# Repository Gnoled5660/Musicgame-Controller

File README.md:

# Musicgame-Controller

# Description
This is an arcade like controller, designed for the Musicgame by bakedcloudz (GitHub Repo: https://github.com/wuelaineyuan-bit/MUSICGAME). It has four interactive buttons and one joystick. Next to these features, it also has a speaker on the side and a tft display. While the controller is inactive or is not being used, it will play a retro arcade like music in the background. All this is powered by a Raspberry Pi Pico 2.

# Motivation
The reason we designed this was because bakedcloudz project lacked of an interactive controller for her arcade game. Therefore, we wanted to design another controller for that project. This project is a sub project of the main project MUSICGAME (GitHub Repo: https://github.com/wuelaineyuan-bit/MUSICGAME). 

# PCB and Schematic
The PCB and schematic was made with KiCAD. Schematic is rather simple: Connect the pins to the buttons and joysticks. As almost every Pico 2 pin is a GPIO pin, almost every pin could be used to connect to the amplifier and tft module. 

This PCB is a rather simple PCB, where the premade modules are soldered on top of it. There are no components that need to be preassembled. All the components are big enough to be soldered by hand. 

This PCB is a two layer PCB, where the red tracks function as signal tracks and the blue tracks as power supply tracks.

# Firmware
The firmware was written in micropython. Most of libraries are standard libraries provided by micropico. However, we had to download an external library for the tft display. The program begins with playing a retro music until one button is clicked. Then, it stops playing the music in a loop and starts listening to the actions that the user might take. Once a button or the joystick is pressed, it sends a message to the computer with the print() function. The other projects code has to read the lines with serial.readline() to decide which actions to make next.

# Assembling
There are a few components that need to be screwed on to the board. These components include the PCB, the joystick and the display. Because of that, we designed some holes, where heat threaded inserts can be placed. All components use M3 screws besides the joystick. The joystick requires M5 screws. The buttons can be simply pressed into the holes, which means it doesnt require any screws. 

Many components need to be soldered on to the PCB too. It is recommended to use header pins between the Pico 2 board and the PCB. After everything is soldered, you need the connection cables to connect the PCB with the buttons and joysticks. Another cable is used to connect the amplifier with the speaker.

Depending on whether you want to color the music notes, there two versions of this controller. As a usual 3D printer cannot print two colors at the same time, the music notes have to be painted later by hand, if they should be colored black.

# Zine

# BOM
|Name                   |Description                  |Links                                                                                                                                                                                                                                                                                                                                                                                                                            |Quantity|Cost |
|-----------------------|-----------------------------|---------------------------------------------------------------------------------------------------------------------------------------------------------------------------------------------------------------------------------------------------------------------------------------------------------------------------------------------------------------------------------------------------------------------------------|--------|-----|
|PCB                    |Printed Circuit Board        |https://jlcpcb.com                                                                                                                                                                                                                                                                                                                                                                                                               |1       |6    |
|Speaker                |8Ohm 1W Speaker              |https://botland.de/analoge-lautsprecher/19458-lautsprecher-1w-8ohm-30x20x5mm-adafruit-4227-5904422354848.html?gad_source=1&gad_campaignid=23574294202&gbraid=0AAAAApBhtfdmZRY2FJGh-xArvpZV2eCLa&gclid=CjwKCAjw9NjRBhATEiwA_p2J8S86mPfKDnuq3Meckbowv6KXXqRWsGLSo_4u3SZHp3daIj2UEHCkihoC-4IQAvD_BwE                                                                                                                                |1       |3.20 |
|MAX98357A              |Amplifier                    |https://www.amazon.de/Verstärker-Verstärkerplatine-Elektronische-Enthusiasten-Ingenieure/dp/B0F1TRSD2N/ref=asc_df_B0F1TRSD2N?mcid=b3cc78920c783042ac17388eb574bcae&th=1&psc=1&tag=googshopde-21&linkCode=df0&hvadid=751200241164&hvpos=&hvnetw=g&hvrand=557849342057074083&hvpone=&hvptwo=&hvqmt=&hvdev=c&hvdvcmdl=&hvlocint=&hvlocphy=9192175&hvtargid=pla-2419607785174&psc=1&hvocijid=557849342057074083-B0F1TRSD2N-&hvexpln=0|1       |8    |
|Pico 2                 |Microcontroller              |https://www.reichelt.de/de/de/shop/produkt/raspberry_pi_pico_2_rp235x_cortex-m33_microusb-383358?PROVID=2788&gad_source=1&gad_campaignid=18342381572&gbraid=0AAAAADwnxtZySp6snfqlNQh9cQN6eEoma&gclid=CjwKCAjw9NjRBhATEiwA_p2J8Z5EgQVT_I2qJDtdCrQ07205wtKj9qcaRFiQCRmb6aA3hme78elB0xoCkwoQAvD_BwE                                                                                                                                 |1       |5.14 |
|Arcade Button          |Button                       |https://www.berrybase.de/mini-arcade-button-24mm/farbe-rot?gad_source=1&gad_campaignid=22735754544&gbraid=0AAAAADSQJK6oAGUJjXrYG5gYnJHQ5Jjam&gclid=CjwKCAjw9NjRBhATEiwA_p2J8TrWjbhcsVNdGDTCZIJtp7aCs2650nWhUSuZ5SYqhxaVa3eP51LD4BoCi0oQAvD_BwE                                                                                                                                                                                   |4       |4.13 |
|Joystick               |Joystick to control direction|https://de.aliexpress.com/item/1005006881757851.html?spm=a2g0o.tesla.0.0.5f0cIGAYIGAYAg&pdp_npi=6%40dis%21EUR%2110%2C38€%214%2C69€%21%21%21%21%21%40211b6c1717819569630011453e4670%2112000038607187018%21btfpre%21%21%21%211%210%21&pvid=210f2bc9-ea8b-413f-9403-466b57ef5987&afTraceInfo=1005006881757851__pc__c_ppc_item_bridge_pc_same_wf__r6YWpYS__1781956963362&gatewayAdapt=glo2deu                                        |1       |12.61|
|5 Pin JST-XH           |Receptacle for Joystick      |https://www.reichelt.de/de/de/shop/produkt/jst_-_stiftleiste_gerade_1x5-polig_-_xh-185076?PROVID=2788&gad_source=1&gad_campaignid=21154722893&gbraid=0AAAAADwnxtbPyJx8nCOWbAD8uZL35tp4z&gclid=CjwKCAjw9NjRBhATEiwA_p2J8V1nQh1DAOTZbzkY9tsnYV5dJ24D084mqzUnY8sjf2c5BYI_QxigaBoCw18QAvD_BwE                                                                                                                                        |1       |0.34 |
|2 Pin JST-XH           |Receptacle for Buttoms       |https://www.berrybase.de/ph2.0-buchse-printmontage-gerade-2-pin?gad_source=1&gad_campaignid=22735754544&gbraid=0AAAAADSQJK6oAGUJjXrYG5gYnJHQ5Jjam&gclid=CjwKCAjw9NjRBhATEiwA_p2J8Urol7tXOTt939yNAB6z-nwgtlo3U0Lzd1b4rYRmLl3-F9V2eJTBkRoC8gwQAvD_BwE                                                                                                                                                                              |4       |0.46 |
|2 Pin JST-XH cable     |Cable                        |https://www.berrybase.de/kabel-mit-jst-xh-2.54mm-steckverbinder-awg26-20cm/pinanzahl-2-pin?gad_source=1&gad_campaignid=22735754544&gbraid=0AAAAADSQJK6oAGUJjXrYG5gYnJHQ5Jjam&gclid=CjwKCAjw9NjRBhATEiwA_p2J8W0x6WuNUUs6bxL4TG9hyvZCpREeYp3Er9v8SU3_aX8OdhUF2LM27hoCtJoQAvD_BwE                                                                                                                                                   |4       |1.60 |
|5 Pin JST-XH cable     |Cable                        |https://www.berrybase.de/kabel-mit-jst-xh-2.54mm-steckverbinder-awg26-20cm/pinanzahl-5-pin?gad_source=1&gad_campaignid=22735754544&gbraid=0AAAAADSQJK6oAGUJjXrYG5gYnJHQ5Jjam&gclid=CjwKCAjw9NjRBhATEiwA_p2J8ed_m7wkuAmCj3BJHQQX81vanObY6mg6JzyN2FSQFX1OP-F2Mh5QaRoCbrMQAvD_BwE                                                                                                                                                   |1       |0.57 |
|Header Pin             |2.54mm Header Pin            |https://www.digikey.de/de/products/detail/amphenol-icc-fci-/10129378-920003BLF/7915971?gclsrc=aw.ds&gad_source=1&gad_campaignid=20475954717&gbraid=0AAAAADrbLliANvk-4k_iHnkN0w1_Owx2g&gclid=CjwKCAjw9NjRBhATEiwA_p2J8enJV0joqofnp_be1iUuoErMy9oAMu6LXCxdTL6W0V9_86SqaJBf5RoC0BYQAvD_BwE                                                                                                                                          |1       |0.52 |
|Heated threaded inserts|M3x4mmx5mm                   |https://www.berrybase.de/bossard-bn1052-gewindeeinsatz-messing-m3-laenge-5-8mm?gad_source=1&gad_campaignid=22735754544&gbraid=0AAAAADSQJK6oAGUJjXrYG5gYnJHQ5Jjam&gclid=CjwKCAjw9NjRBhATEiwA_p2J8fmtN9uvJFi6raxtH1SBm7bqzLmf6tLV8yUB9gSUcvRfArNPB06mJhoCuyUQAvD_BwE                                                                                                                                                               |8       |2.58 |
|Heated threaded inserts|M5x9mmx5mm                   |https://www.berrybase.de/bossard-bn1052-gewindeeinsatz-messing-m5-laenge-9-5mm?gad_source=1&gad_campaignid=22735754544&gbraid=0AAAAADSQJK6oAGUJjXrYG5gYnJHQ5Jjam&gclid=CjwKCAjw9NjRBhATEiwA_p2J8eEpl-ngpjr0zGPOqsMol5EgsN96HSMkL-J5gVBillc_oGD0vaZc2xoCkN8QAvD_BwE                                                                                                                                                               |4       |1.28 |
|M3                     |screws                       |https://www.berrybase.de/makerbeam-linsenkopfschrauben-fuer-15x15-makerbeamxl-openbeam-m3x6mm-innensechskant-100-stueck?gad_source=1&gad_campaignid=22735754544&gbraid=0AAAAADSQJK6oAGUJjXrYG5gYnJHQ5Jjam&gclid=CjwKCAjw9NjRBhATEiwA_p2J8c6O3telypadqSWUnIosaG3yVkbjvgmMxDbh4MoW5Eh82wFQ_xoHuBoCRpoQAvD_BwE                                                                                                                      |8       |6    |
|M5                     |screws                       |https://www.thomann.de/de/km_m5_rack_screw_pack.htm?gad_source=1&gad_campaignid=1576042954&gbraid=0AAAAADuDMCXMyqF9VJSCZggPhx_6MjWGL&gclid=CjwKCAjw9NjRBhATEiwA_p2J8ayVorCc0uU63e3y15L2IY4ynFoCtjSuOSQzXwZ0U_juIpEPnycZ4hoCz3QQAvD_BwE                                                                                                                                                                                           |4       |4    |
|Filament               |Whole Case                   |                                                                                                                                                                                                                                                                                                                                                                                                                                 |1       |8.93 |
|total                  |                             |                                                                                                                                                                                                                                                                                                                                                                                                                                 |        |63.19|

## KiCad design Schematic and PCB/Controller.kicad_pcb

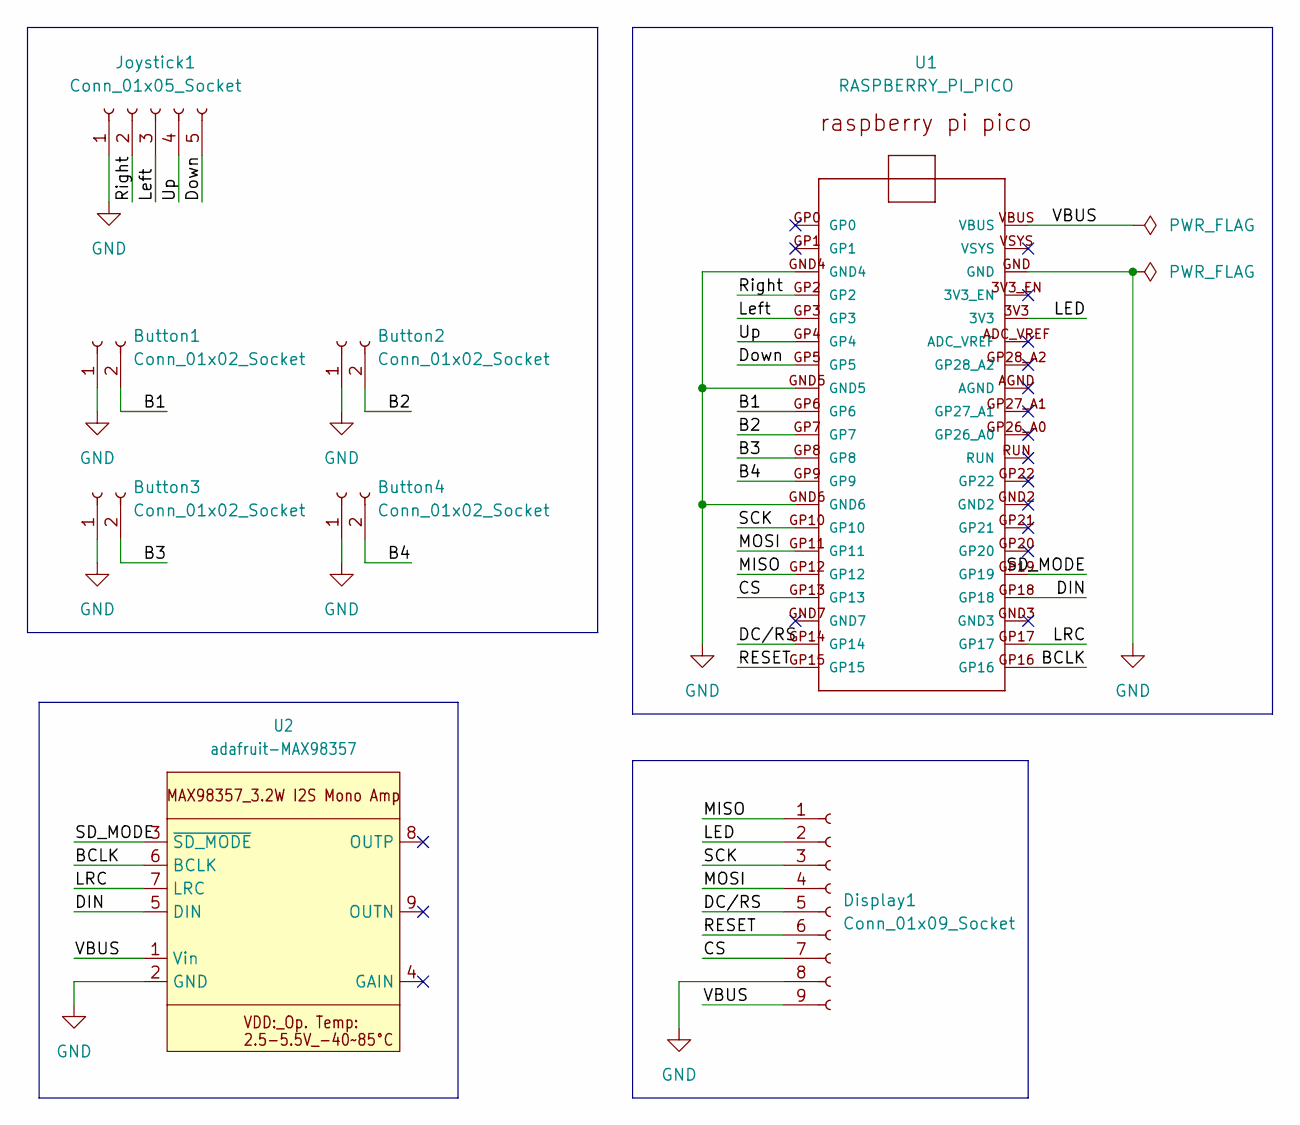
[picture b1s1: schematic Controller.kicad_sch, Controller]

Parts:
Button1, Button2, Button3, Button4: Conn_01x02_Socket; JST_XH_B2B-XH-A_1x02_P2.50mm_Vertical
Display1: Conn_01x09_Socket; PinHeader_1x09_P2.54mm_Vertical
Joystick1: Conn_01x05_Socket; JST_XH_B5B-XH-A_1x05_P2.50mm_Vertical
U1: RASPBERRY_PI_PICO
U2: adafruit-MAX98357

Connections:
/B1: Button1.2, U1.GP6
/B2: Button2.2, U1.GP7
/B3: Button3.2, U1.GP8
/B4: Button4.2, U1.GP9
/BCLK: U1.GP16, U2.6 (BCLK)
/CS: Display1.7, U1.GP13
/DC/RS: Display1.5, U1.GP14
/DIN: U1.GP18, U2.5 (DIN)
/Down: Joystick1.5, U1.GP5
/LED: Display1.2, U1.3V3
/LRC: U1.GP17, U2.7 (LRC)
/Left: Joystick1.3, U1.GP3
/MISO: Display1.1, U1.GP12
/MOSI: Display1.4, U1.GP11
/RESET: Display1.6, U1.GP15
/Right: Joystick1.2, U1.GP2
/SCK: Display1.3, U1.GP10
/SD_MODE: U1.GP19, U2.3 (~SD_MODE)
/Up: Joystick1.4, U1.GP4
/VBUS: Display1.9, U1.VBUS, U2.1 (Vin)
GND: Button1.1, Button2.1, Button3.1, Button4.1, Display1.8, Joystick1.1, U1.GND, U1.GND4, U1.GND5, U1.GND6, U2.2 (GND)

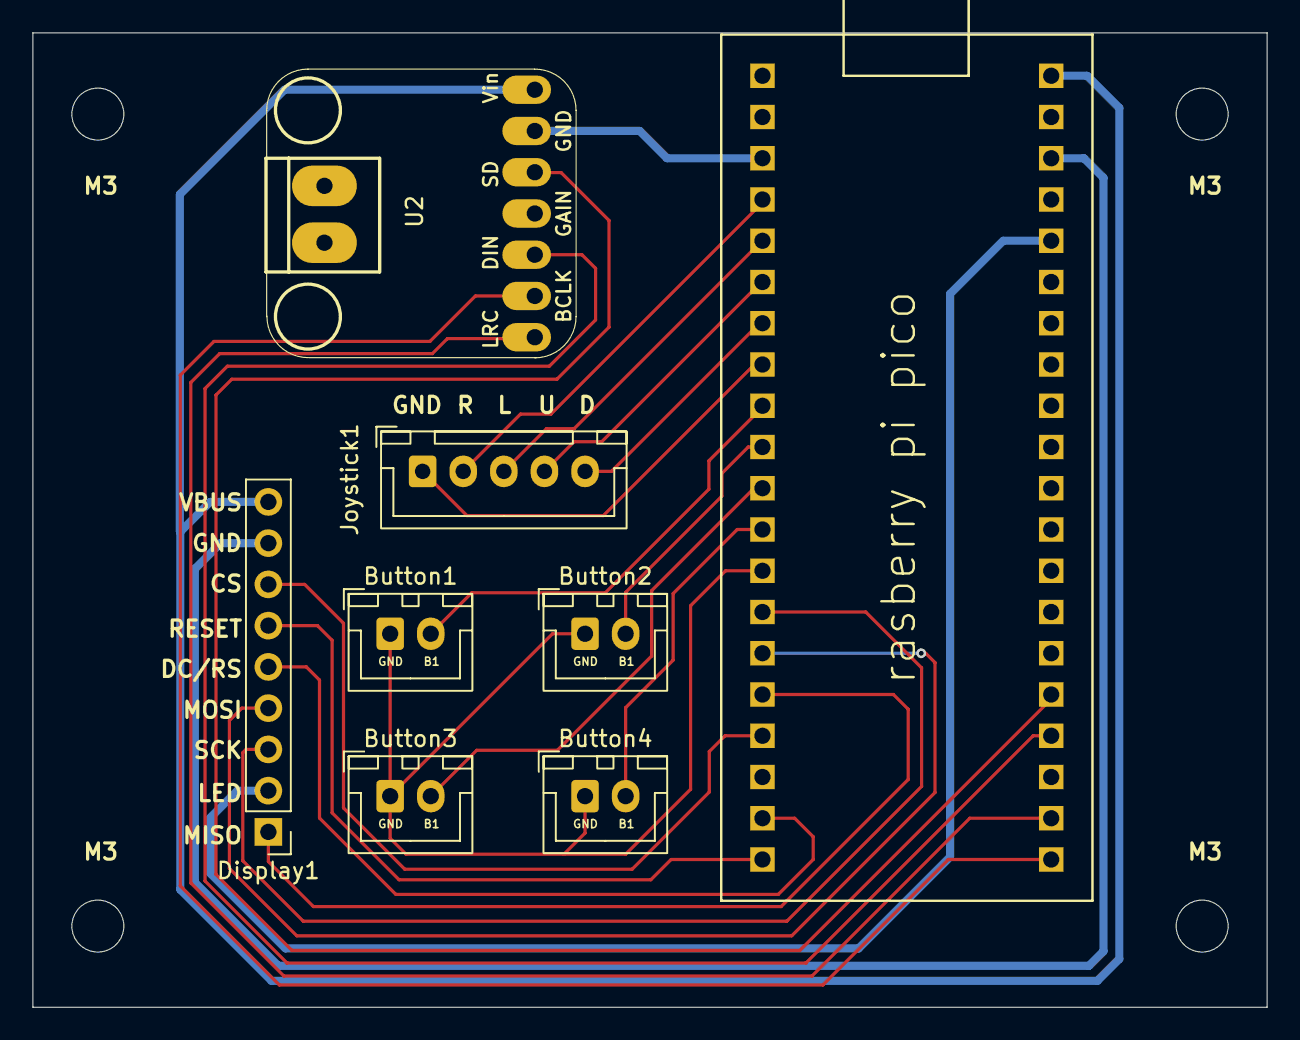
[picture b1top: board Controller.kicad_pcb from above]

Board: 2 copper layers, 76.0 x 60.0 mm, 8 parts (0 on the bottom side), 21 nets.

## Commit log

2026-06-19 Create w
2026-06-20 Just Tests
2026-06-20 Unfinished code
2026-06-20 finished firmware
2026-06-20 Rename Bottom Case.step to Case Bottom.step
2026-06-20 Rename Top Case.step to Case Top.step
2026-06-20 Rename Unbenannte Tabelle - Tabellenblatt1-2.csv to BOM.csv
2026-06-20 Update PCB assembly instructions in README
    Added instructions for connecting cables after soldering components.
2026-06-20 Rename Your paragraph text (5.83 x 8.27 in).pdf to Zine.pdf
2026-06-20 Rename Your paragraph text (5.83 x 8.27 in).png to Zine.png
2026-06-20 Create temp
